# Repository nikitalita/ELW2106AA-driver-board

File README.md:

# ELW2106AA-driver-board
driver board for the ELW2106AA

WARNING: COMPLETELY UNTESTED

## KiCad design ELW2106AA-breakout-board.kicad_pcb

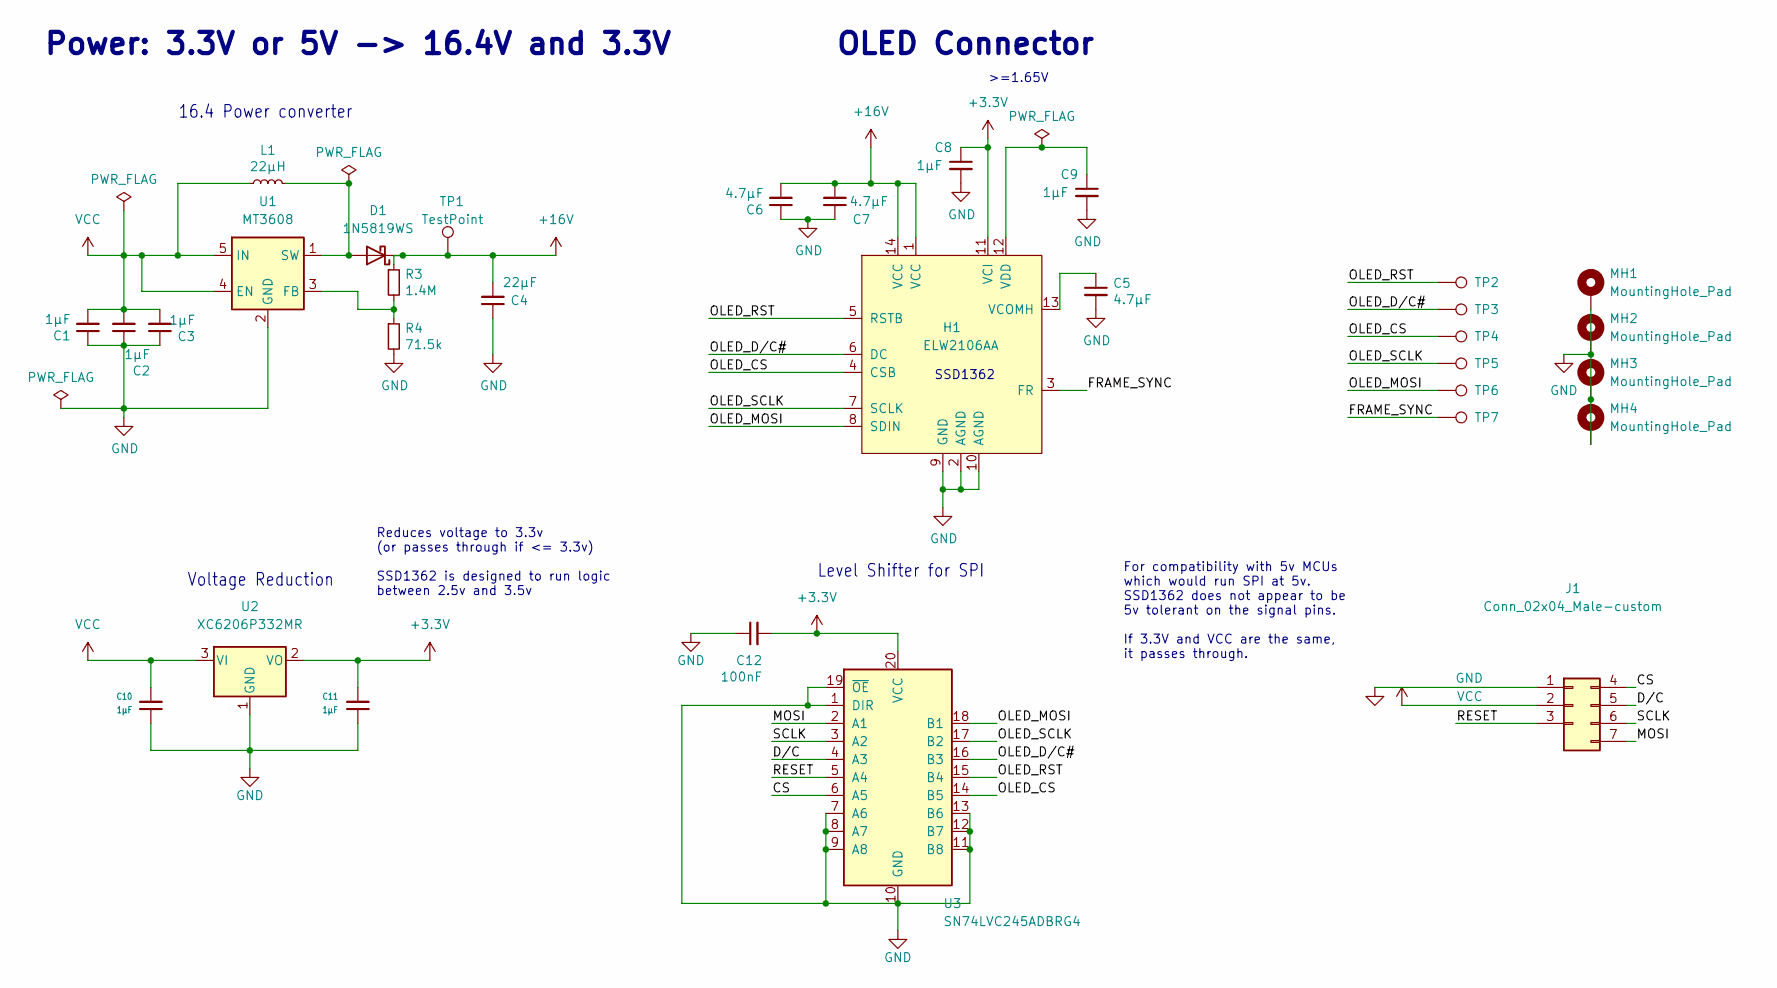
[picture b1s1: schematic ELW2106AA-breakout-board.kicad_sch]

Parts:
C1, C2, C3, C8, C9, C10, C11: 1µF; C_0402_1005Metric; LCSC C52923
C4: 22µF; C_0805_2012Metric; LCSC C45783
C5, C6, C7: 4.7µF; C_0402_1005Metric; LCSC C1550
C12: 100nF; C_0402_1005Metric
D1: 1N5819WS; D_SOD-323; LCSC C440261
H1: ELW2106AA; AFC24-S14FIA-00; MPN 503480-1400; Farnell 3215747
J1: Conn_02x04_Male-custom; PinHeader_2x04_P2.54mm_Vertical-custom
L1: 22µH; L_1812_4532Metric; MPN LQH43PN220M26L; Farnell 2219279
MH1, MH2, MH3, MH4: MountingHole_Pad; MountingHole_2.2mm_M2_Custom_Pad
R3: 1.4M; R_0402_1005Metric; LCSC C270644
R4: 71.5k; R_0402_1005Metric; LCSC C43534
TP1: TestPoint; TestPoint_Pad_D1.5mm
TP2, TP3, TP4, TP5, TP6, TP7: TestPoint; TestPoint_Pad_D1.0mm
U1: MT3608; SOT-23-6; LCSC C7846
U2: XC6206P332MR; SOT-23; LCSC C479053
U3: SN74LVC245ADBRG4; SOP65P640X120-20N; LCSC C7848

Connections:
+3V3: C8.1, C11.2, C12.2, H1.11 (VCI), U2.2 (VO), U3.20 (VCC)
+16V: C4.2, C6.2, C7.2, D1.1 (K), H1.1 (VCC), H1.14 (VCC), R3.1, TP1.1
/CS: J1.4, U3.6 (A5)
/D/C: J1.5, U3.4 (A3)
/FRAME_SYNC: H1.3 (FR), TP7.1
/MOSI: J1.7, U3.2 (A1)
/OLED_CS: H1.4 (CSB), TP4.1, U3.14 (B5)
/OLED_D/C#: H1.6 (DC), TP3.1, U3.16 (B3)
/OLED_MOSI: H1.8 (SDIN), TP6.1, U3.18 (B1)
/OLED_RST: H1.5 (RSTB), TP2.1, U3.15 (B4)
/OLED_SCLK: H1.7 (SCLK), TP5.1, U3.17 (B2)
/RESET: J1.3, U3.5 (A4)
/SCLK: J1.6, U3.3 (A2)
GND: C1.1, C2.1, C3.1, C4.1, C5.2, C6.1, C7.1, C8.2, C9.2, C10.1, C11.1, C12.1, H1.2 (AGND), H1.9 (GND), H1.10 (AGND), J1.1, MH1.1, MH2.1, MH3.1, MH4.1, R4.2, U1.2 (GND), U2.1 (GND), U3.1 (DIR), U3.7 (A6), U3.8 (A7), U3.9 (A8), U3.10 (GND), U3.11 (B8), U3.12 (B7), U3.13 (B6), U3.19 (~OE)
unnamed: C5.1, H1.13 (VCOMH)
unnamed: C9.1, H1.12 (VDD)
unnamed: D1.2 (A), L1.2, U1.1 (SW)
unnamed: R3.2, R4.1, U1.3 (FB)
VCC: C1.2, C2.2, C3.2, C10.2, J1.2, L1.1, U1.4 (EN), U1.5 (IN), U2.3 (VI)

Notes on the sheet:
Power: 3.3V or 5V -> 16.4V and 3.3V
Level Shifter for SPI
Voltage Reduction
SSD1362
>=1.65V
For compatibility with 5v MCUs which would run SPI at 5v. SSD1362 does not appear to be 5v tolerant on the signal pins. If 3.3V and VCC are the same, it passes through.
OLED Connector
Reduces voltage to 3.3v (or passes through if <= 3.3v) SSD1362 is designed to run logic between 2.5v and 3.5v
16.4 Power converter

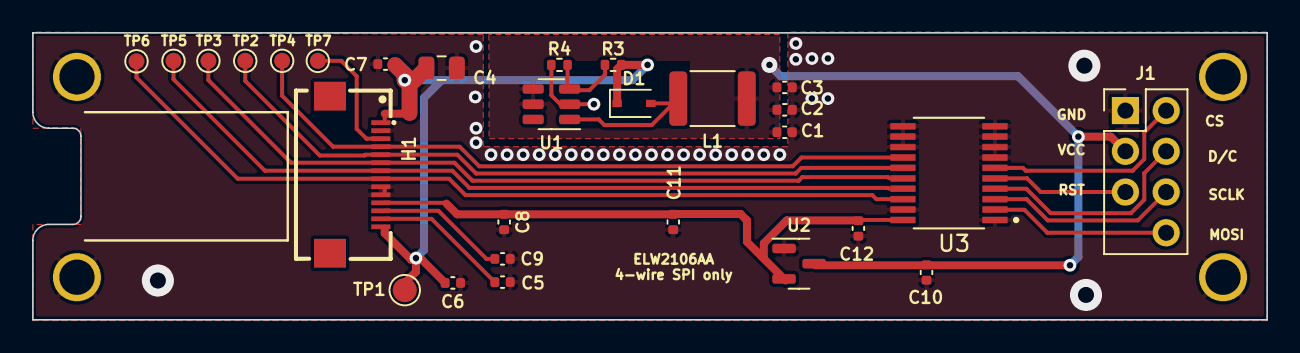
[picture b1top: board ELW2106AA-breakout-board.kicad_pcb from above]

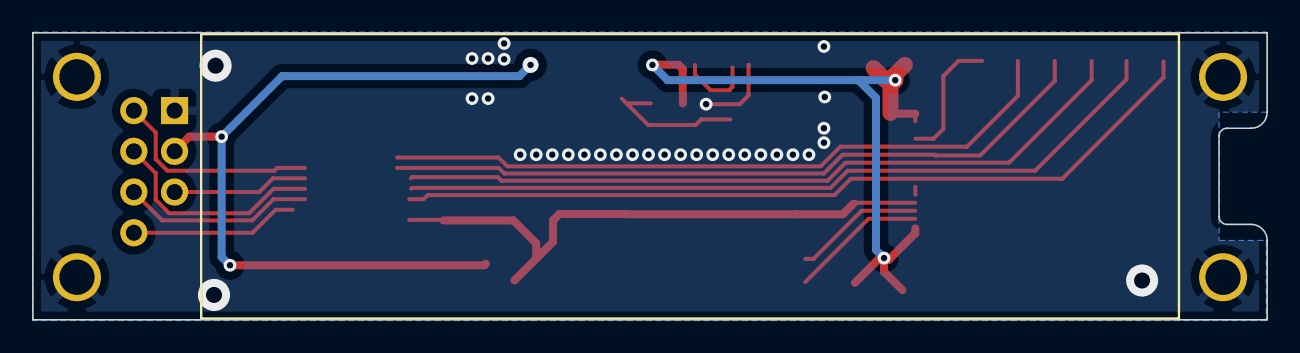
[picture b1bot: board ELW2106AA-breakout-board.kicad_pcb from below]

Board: 2 copper layers, 77.0 x 17.9 mm, 32 parts (4 on the bottom side), 19 nets.

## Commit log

2022-03-18 initial files
2022-03-18 update 3d model
2022-03-18 second revision
2022-03-18 third revision
2022-03-19 replace TXS0108E with good ol' SN74LVC245
2022-03-30 final draft, add jlcpcb information for fabbing/assembly
